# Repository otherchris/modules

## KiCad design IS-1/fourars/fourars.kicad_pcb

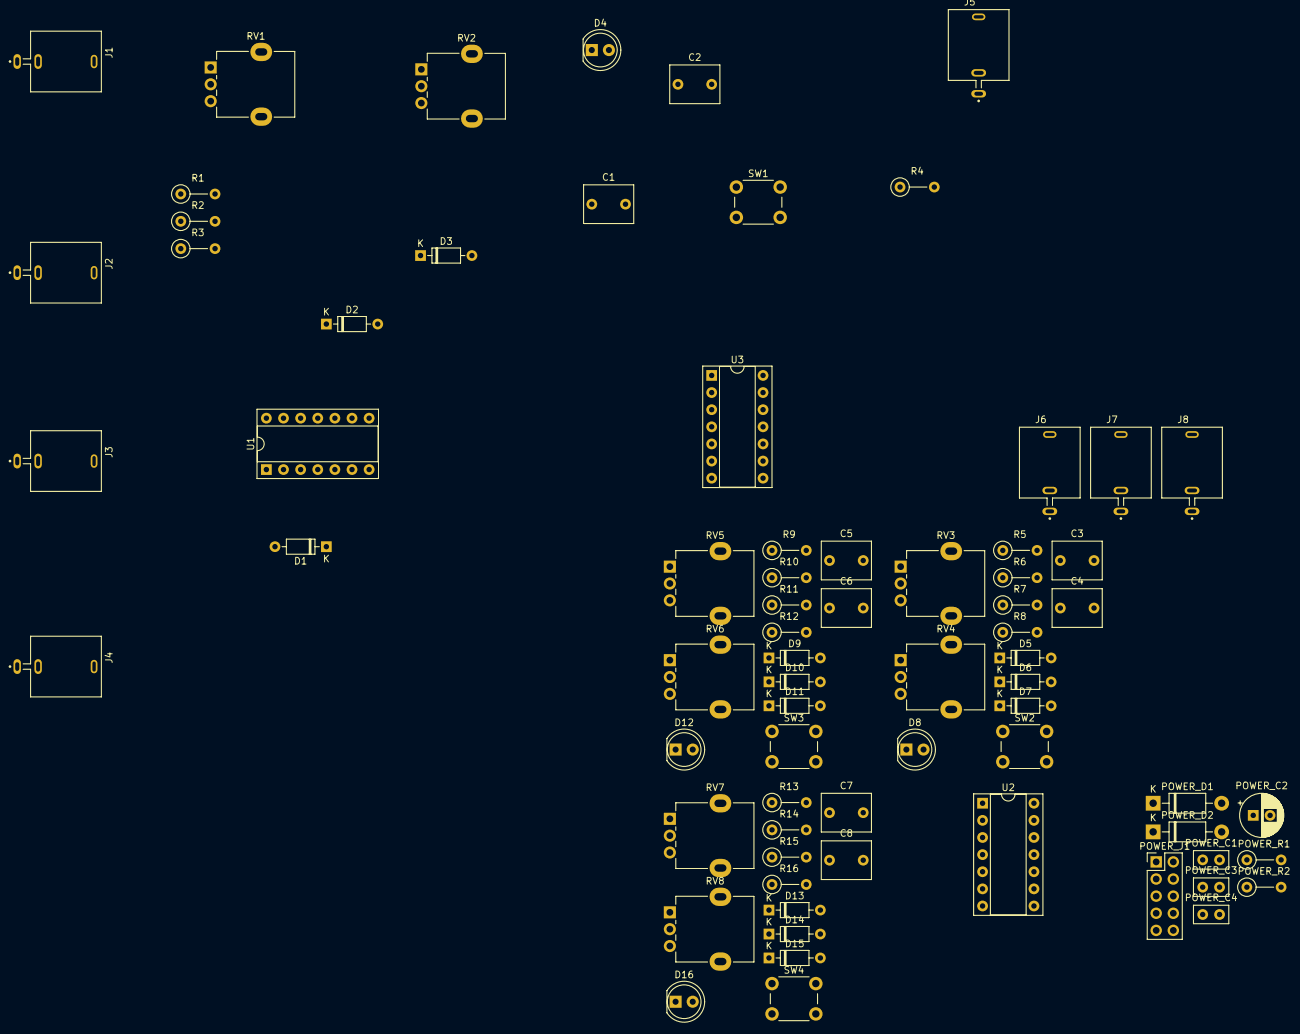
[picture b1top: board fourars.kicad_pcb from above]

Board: 2 copper layers, 72 parts (0 on the bottom side), 55 nets, no tracks yet.

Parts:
C1, C2, C3, C4, C5, C6, C7, C8: c=1u; C_Rect_L7.2mm_W5.5mm_P5.00mm_FKS2_FKP2_MKS2_MKP2
D1, D2, D3, D5, D6, D7, D9, D10, D11, D13, D14, D15: 1N4148; D_DO-35_SOD27_P7.62mm_Horizontal
D4, D8, D12, D16: LED; LED_D5.0mm_FlatTop
J1, J2, J3, J4, J5, J6, J7, J8: PJ398SM-12; THONK_PJ398SM-12
POWER_C1: c=47u; C_Disc_D5.0mm_W2.5mm_P2.50mm
POWER_C2: c=47u; CP_Radial_D6.3mm_P2.50mm
POWER_C3, POWER_C4: 0.1u; C_Disc_D5.0mm_W2.5mm_P2.50mm
POWER_D1, POWER_D2: 1N5819; D_DO-41_SOD81_P10.16mm_Horizontal
POWER_J1: Conn_01x10_Pin; PinHeader_2x05_P2.54mm_Vertical
POWER_R1, POWER_R2: 10; R_Axial_DIN0207_L6.3mm_D2.5mm_P5.08mm_Vertical
R1, R3, R5, R7, R9, R11, R13, R15: r=100k; R_Axial_DIN0207_L6.3mm_D2.5mm_P5.08mm_Vertical
R2, R6, R10, R14: r=47k; R_Axial_DIN0207_L6.3mm_D2.5mm_P5.08mm_Vertical
R4, R8, R12, R16: r=1k; R_Axial_DIN0207_L6.3mm_D2.5mm_P5.08mm_Vertical
RV1, RV2, RV3, RV4, RV5, RV6, RV7, RV8: R_Potentiometer; Potentiometer_Alpha_RD901F-40-00D_Single_Vertical
SW1, SW2, SW3, SW4: SW_SPDT; SW_PUSH_6mm
U1, U2, U3: TL074; DIP-14_W7.62mm_Socket

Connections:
+12v: POWER_C1.1, POWER_C3.1, POWER_R1.2, R1.1, R5.1, R9.1, R13.1, U1.4 (V+), U2.4 (V+), U3.4 (V+)
-12v: POWER_C2.2, POWER_C4.2, POWER_R2.2, U1.11 (V-), U2.11 (V-), U3.11 (V-)
/AR1/ENV_OUT: J5.3, R4.2
/AR1/GATE_IN: J1.3, J2.2, U1.3 (+)
/AR1/INPUT_AMP_-: R1.2, R2.1, U1.2 (-)
/AR1/INPUT_AMP_OUT: D1.2 (A), U1.1
/AR1/INPUT_BUF_+: D1.1 (K), R3.1, U1.5 (+)
/AR1/INPUT_BUF_-: D2.2 (A), D3.1 (K), U1.6 (-), U1.7
/AR1/OUPUT_BUF_OUT: R4.1, U3.1, U3.2 (-)
/AR1/OUTPUT_BUF_+: D4.1 (K), SW1.1 (A), U3.3 (+)
/AR2/ENV_OUT: J6.3, R8.2
/AR2/GATE_IN: J2.3, J3.2, U1.10 (+)
/AR2/INPUT_AMP_-: R5.2, R6.1, U1.9 (-)
/AR2/INPUT_AMP_OUT: D5.2 (A), U1.8
/AR2/INPUT_BUF_+: D5.1 (K), R7.1, U1.12 (+)
/AR2/INPUT_BUF_-: D6.2 (A), D7.1 (K), U1.13 (-), U1.14
/AR2/OUPUT_BUF_OUT: R8.1, U3.6 (-), U3.7
/AR2/OUTPUT_BUF_+: D8.1 (K), SW2.1 (A), U3.5 (+)
/AR3/ENV_OUT: J7.3, R12.2
/AR3/GATE_IN: J3.3, J4.2, U2.3 (+)
/AR3/INPUT_AMP_-: R9.2, R10.1, U2.2 (-)
/AR3/INPUT_AMP_OUT: D9.2 (A), U2.1
/AR3/INPUT_BUF_+: D9.1 (K), R11.1, U2.5 (+)
/AR3/INPUT_BUF_-: D10.2 (A), D11.1 (K), U2.6 (-), U2.7
/AR3/OUPUT_BUF_OUT: R12.1, U3.8, U3.10 (+)
/AR3/OUTPUT_BUF_+: D12.1 (K), SW3.1 (A), U3.9 (-)
/AR4/ENV_OUT: J8.3, R16.2
/AR4/GATE_IN: J4.3, U2.10 (+)
/AR4/INPUT_AMP_-: R13.2, R14.1, U2.9 (-)
/AR4/INPUT_AMP_OUT: D13.2 (A), U2.8
/AR4/INPUT_BUF_+: D13.1 (K), R15.1, U2.12 (+)
/AR4/INPUT_BUF_-: D14.2 (A), D15.1 (K), U2.13 (-), U2.14
/AR4/OUPUT_BUF_OUT: R16.1, U3.12 (+), U3.14
/AR4/OUTPUT_BUF_+: D16.1 (K), SW4.1 (A), U3.13 (-)
GND: C1.2, C2.2, C3.2, C4.2, C5.2, C6.2, C7.2, C8.2, J1.1, J1.2, J2.1, J3.1, J4.1, J5.1, J5.2, J6.1, J6.2, J7.1, J7.2, J8.1, J8.2, POWER_C1.2, POWER_C2.1, POWER_C3.2, POWER_C4.1, POWER_J1.3, POWER_J1.4, POWER_J1.5, POWER_J1.6, POWER_J1.7, POWER_J1.8, R2.2, R3.2, R6.2, R7.2, R10.2, R11.2, R14.2, R15.2
unnamed: D2.1 (K), RV1.1
unnamed: D3.2 (A), RV2.1
unnamed: C2.1, D4.2 (A)
unnamed: D6.1 (K), RV3.1
unnamed: D7.2 (A), RV4.1
unnamed: C4.1, D8.2 (A)
unnamed: D10.1 (K), RV5.1
unnamed: D11.2 (A), RV6.1
unnamed: C6.1, D12.2 (A)
unnamed: D14.1 (K), RV7.1
unnamed: D15.2 (A), RV8.1
unnamed: C8.1, D16.2 (A)
unnamed: POWER_D1.2 (A), POWER_J1.1, POWER_J1.2
unnamed: POWER_D1.1 (K), POWER_R1.1
unnamed: POWER_D2.2 (A), POWER_R2.1
unnamed: POWER_D2.1 (K), POWER_J1.9, POWER_J1.10
unnamed: C1.1, RV1.2, RV1.3, RV2.2, RV2.3, SW1.2 (B)
unnamed: C3.1, RV3.2, RV3.3, RV4.2, RV4.3, SW2.2 (B)
unnamed: C5.1, RV5.2, RV5.3, RV6.2, RV6.3, SW3.2 (B)
unnamed: C7.1, RV7.2, RV7.3, RV8.2, RV8.3, SW4.2 (B)

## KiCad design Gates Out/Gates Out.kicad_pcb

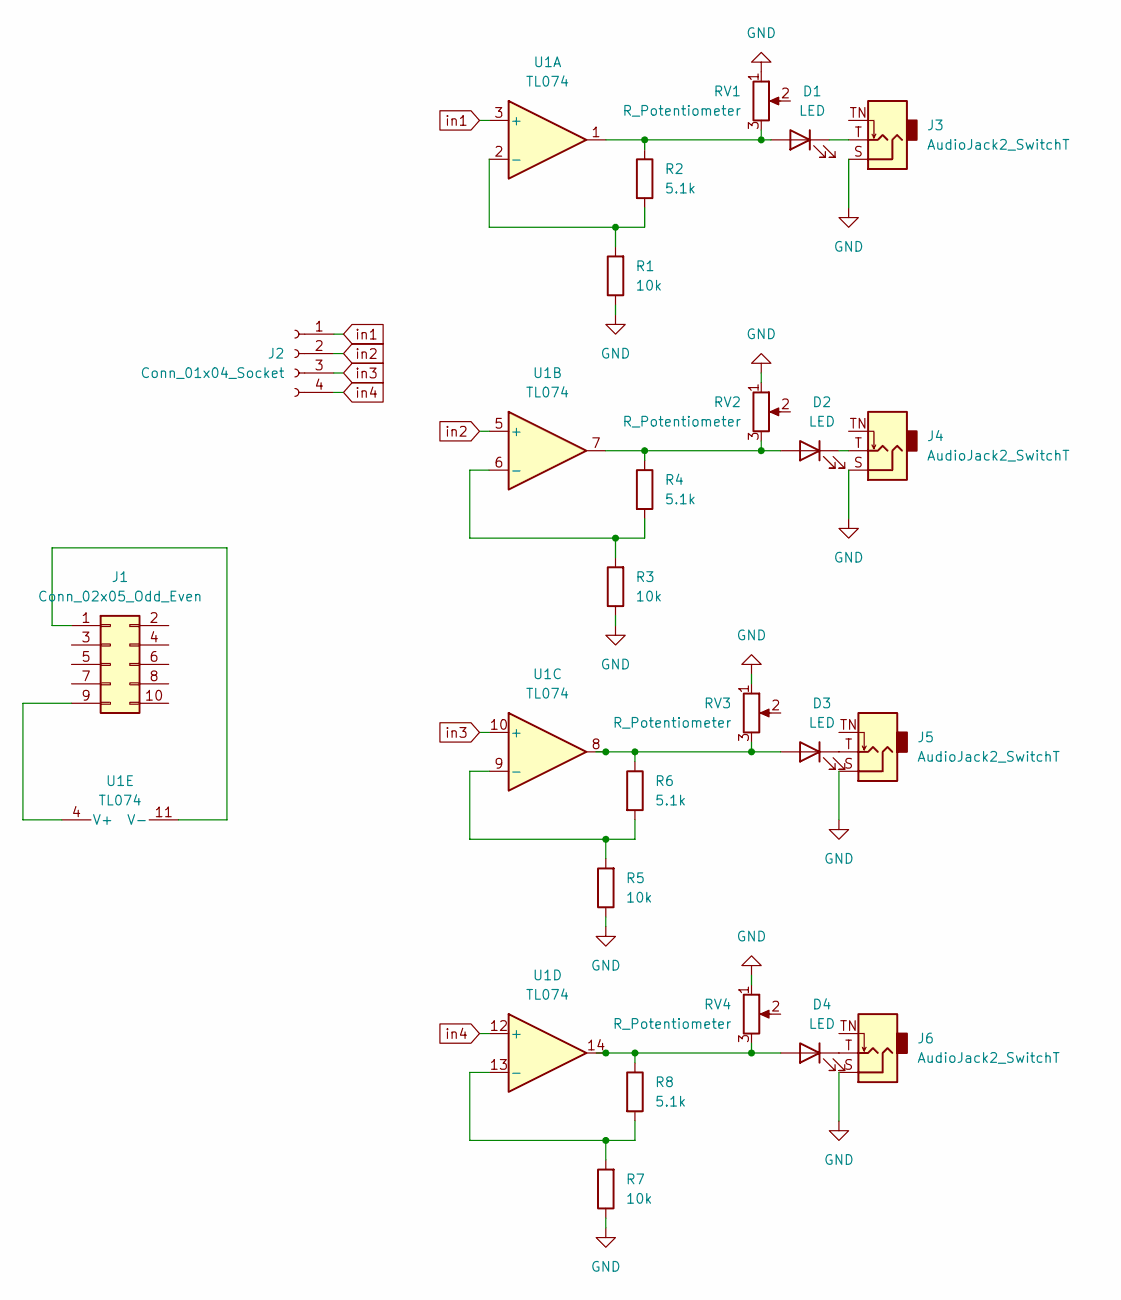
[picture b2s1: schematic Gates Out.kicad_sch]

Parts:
D1, D2, D3, D4: LED; LED_D2.0mm_W4.0mm_H2.8mm_FlatTop
J1: Conn_02x05_Odd_Even; PinHeader_2x05_P2.54mm_Vertical
J2: Conn_01x04_Socket; PinSocket_1x04_P2.54mm_Vertical
J3, J4, J5, J6: AudioJack2_SwitchT; Jack_3.5mm_QingPu_WQP-PJ398SM_Vertical_CircularHoles
R1, R3, R5, R7: 10k; R_Axial_DIN0204_L3.6mm_D1.6mm_P5.08mm_Horizontal
R2, R4, R6, R8: 5.1k; R_Axial_DIN0204_L3.6mm_D1.6mm_P5.08mm_Horizontal
RV1, RV2, RV3, RV4: R_Potentiometer; Potentiometer_Alps_RK09K_Single_Vertical
U1: TL074; DIP-14_W7.62mm_Socket

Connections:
GND: J3.S, J4.S, J5.S, J6.S, R1.1, R3.1, R5.1, R7.1, RV1.1, RV2.1, RV3.1, RV4.1
unnamed: D1.2 (A), R2.1, RV1.3, U1.1
unnamed: D1.1 (K), J3.T
unnamed: D2.2 (A), R4.1, RV2.3, U1.7
unnamed: D2.1 (K), J4.T
unnamed: D3.2 (A), R6.1, RV3.3, U1.8
unnamed: D3.1 (K), J5.T
unnamed: D4.2 (A), R8.1, RV4.3, U1.14
unnamed: D4.1 (K), J6.T
unnamed: J1.1, U1.11 (V-)
unnamed: J1.9, U1.4 (V+)
unnamed: R1.2, R2.2, U1.2 (-)
unnamed: R3.2, R4.2, U1.6 (-)
unnamed: R5.2, R6.2, U1.9 (-)
unnamed: R7.2, R8.2, U1.13 (-)
in1: J2.1, U1.3 (+)
in2: J2.2, U1.5 (+)
in3: J2.3, U1.10 (+)
in4: J2.4, U1.12 (+)

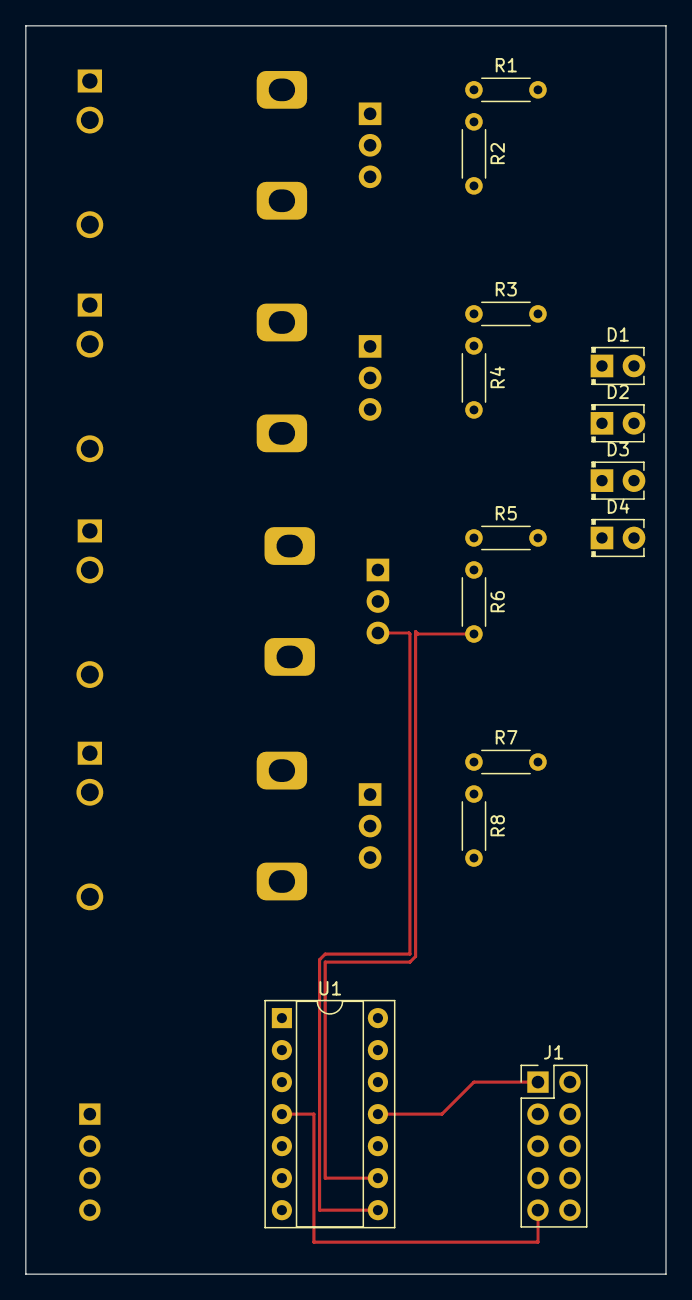
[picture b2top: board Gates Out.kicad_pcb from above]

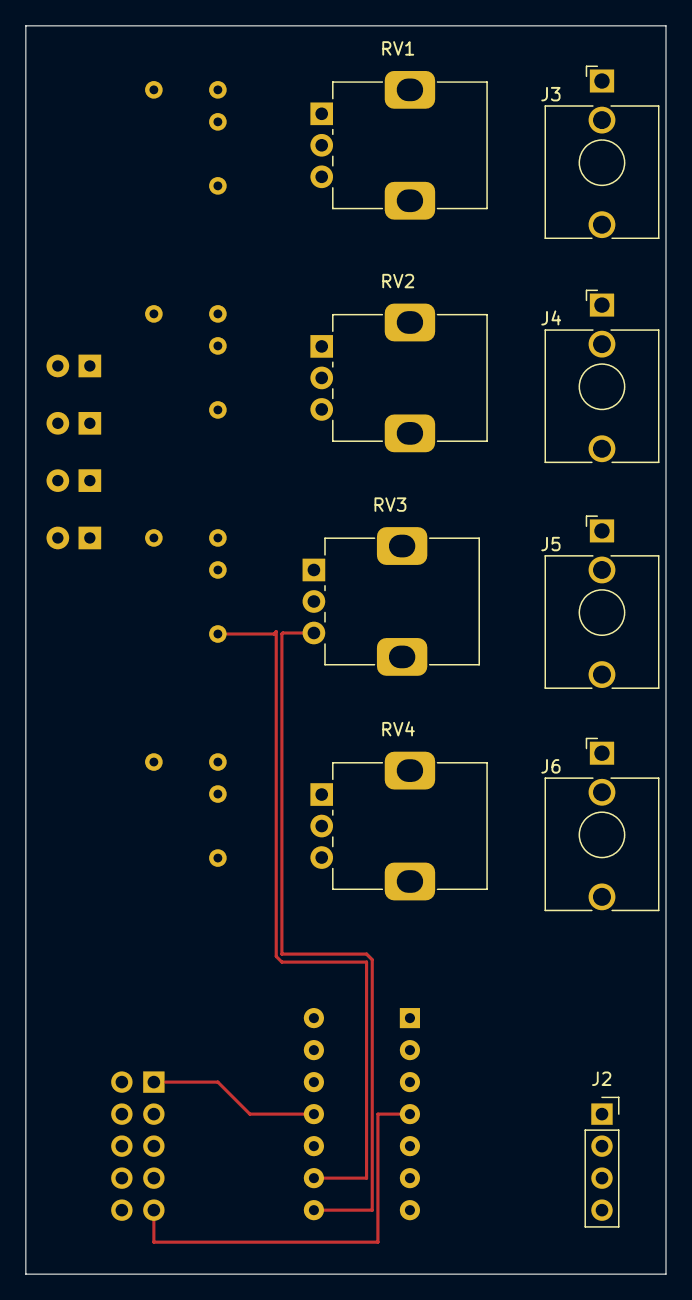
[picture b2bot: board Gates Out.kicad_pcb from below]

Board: 2 copper layers, 50.8 x 99.1 mm, 23 parts (9 on the bottom side), 19 nets.

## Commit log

2023-10-30 ready to pcb
